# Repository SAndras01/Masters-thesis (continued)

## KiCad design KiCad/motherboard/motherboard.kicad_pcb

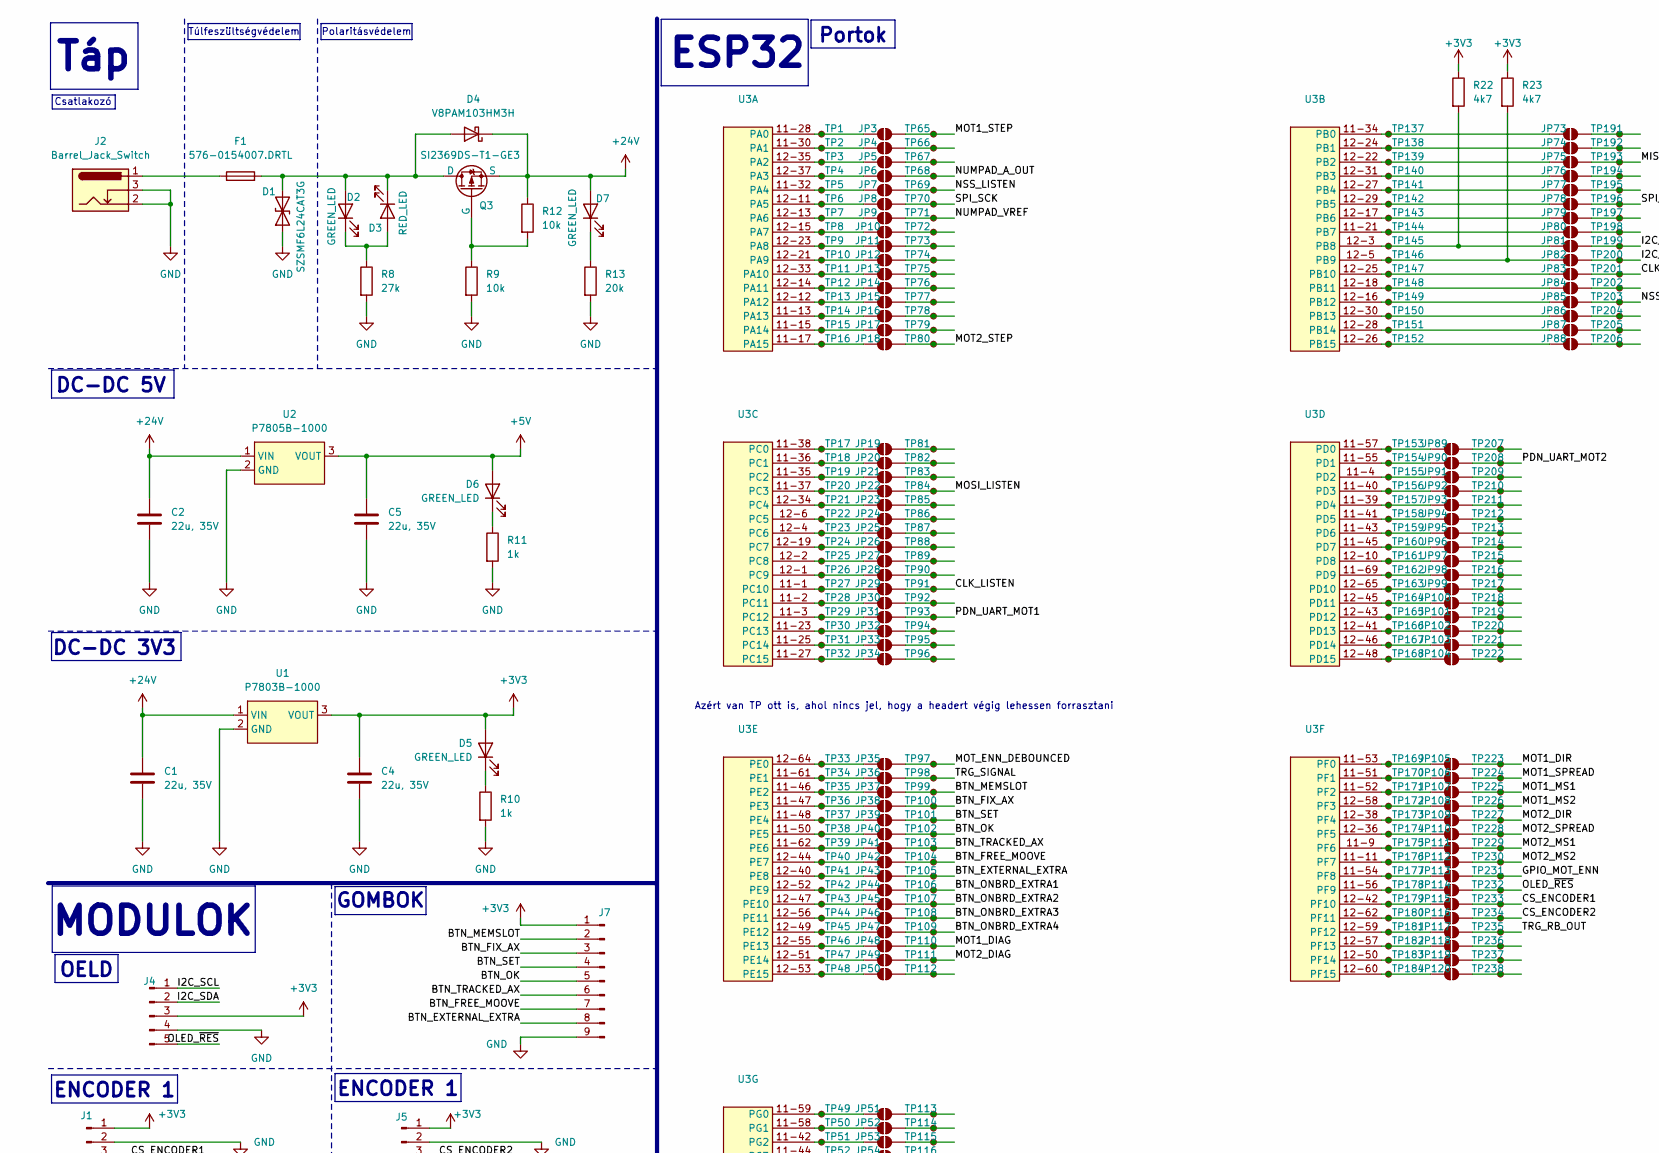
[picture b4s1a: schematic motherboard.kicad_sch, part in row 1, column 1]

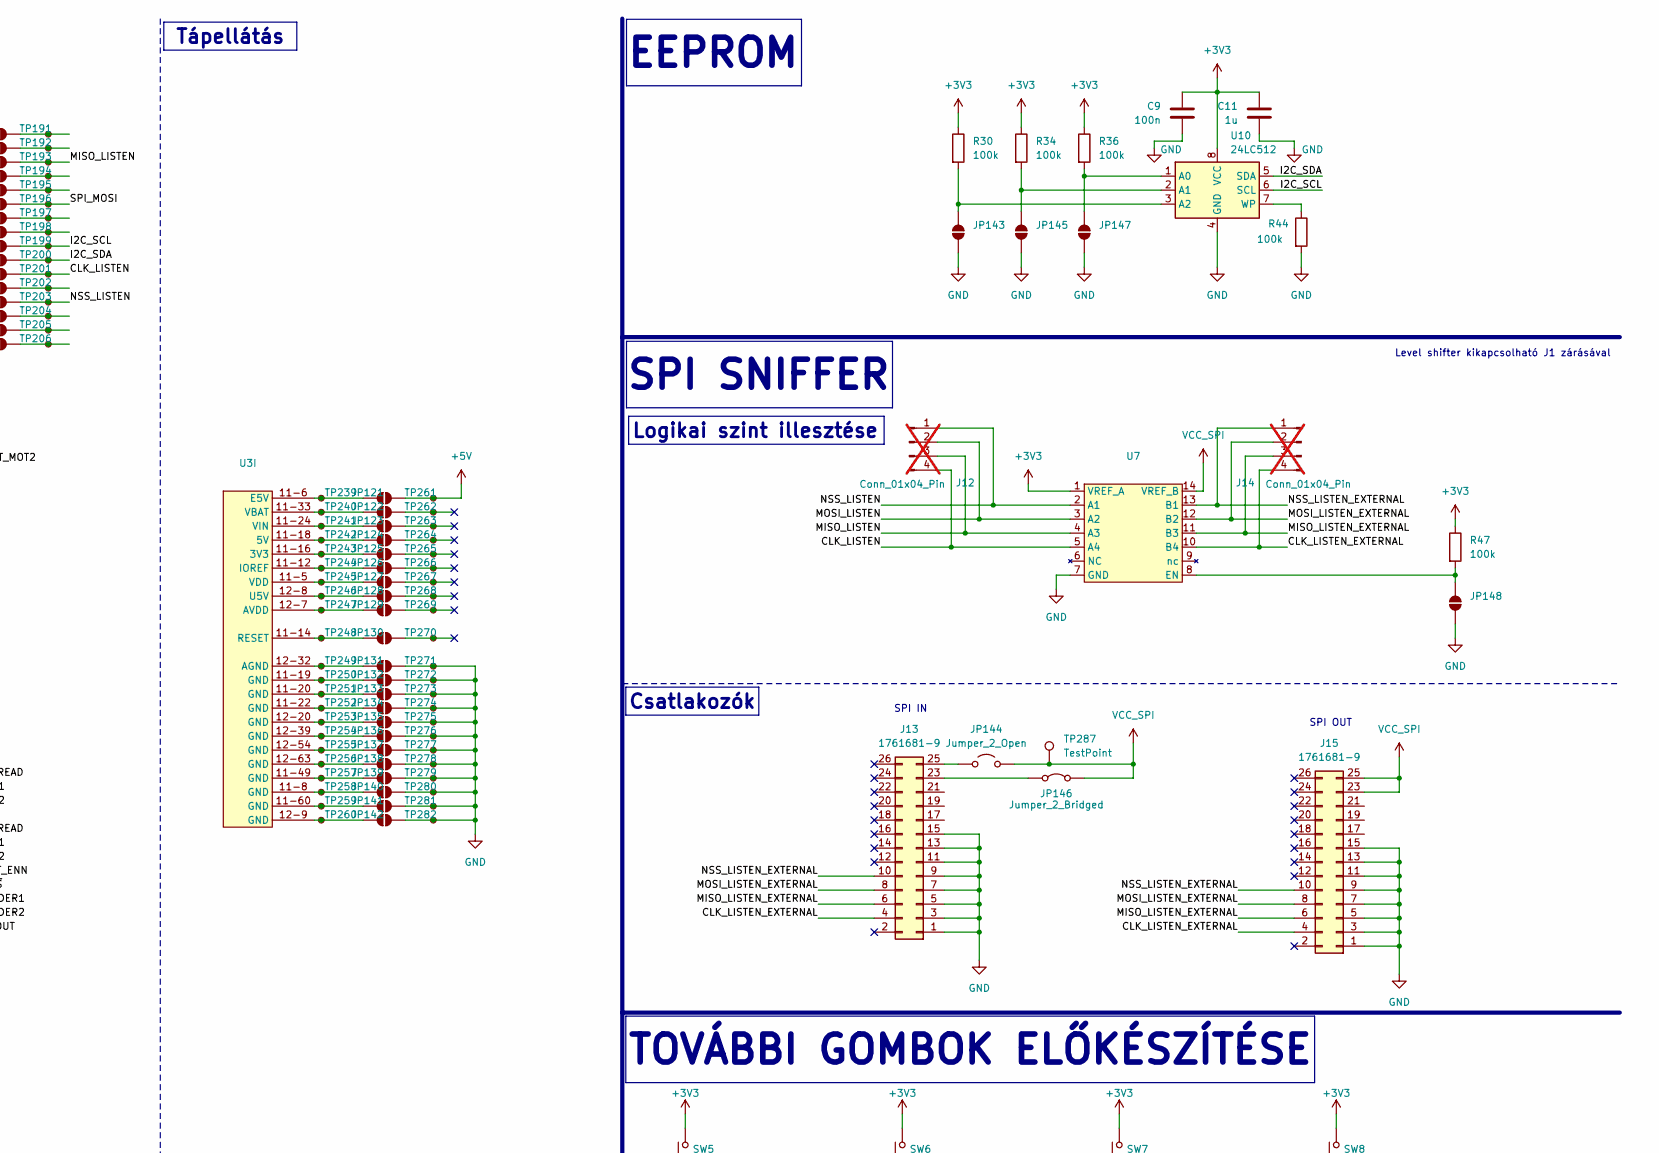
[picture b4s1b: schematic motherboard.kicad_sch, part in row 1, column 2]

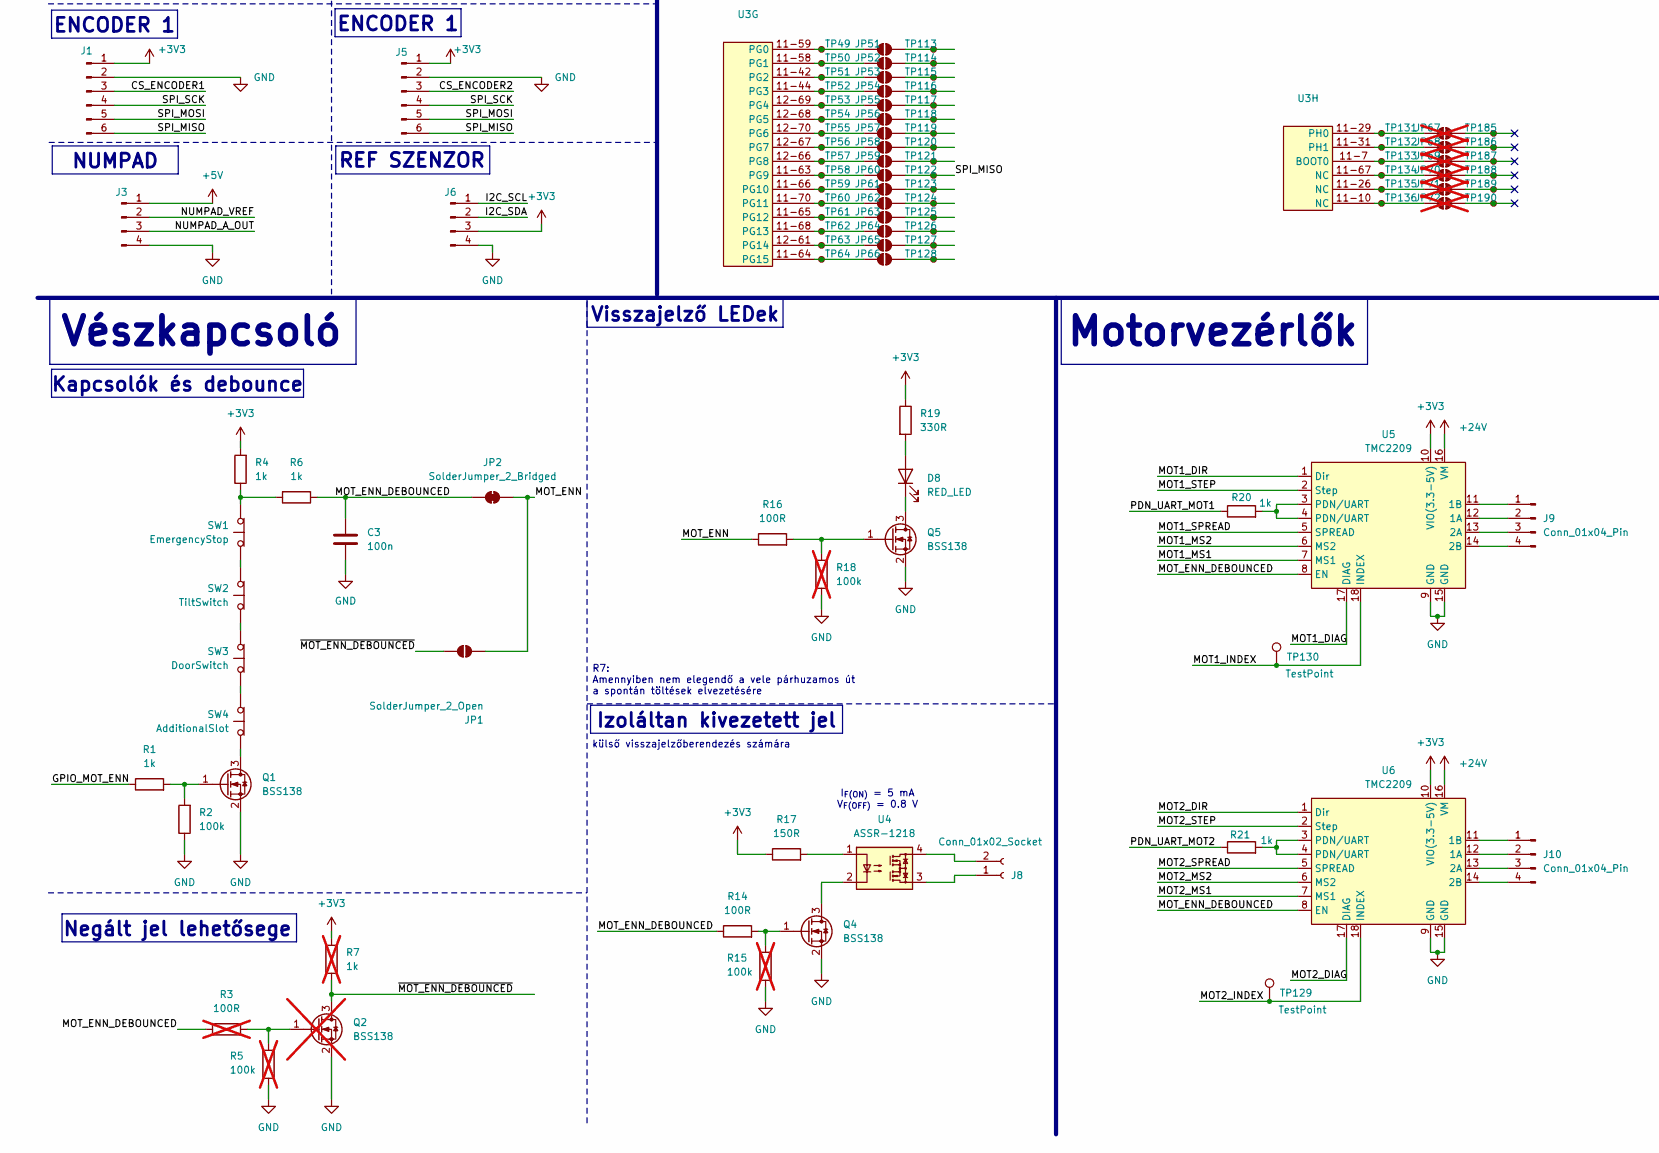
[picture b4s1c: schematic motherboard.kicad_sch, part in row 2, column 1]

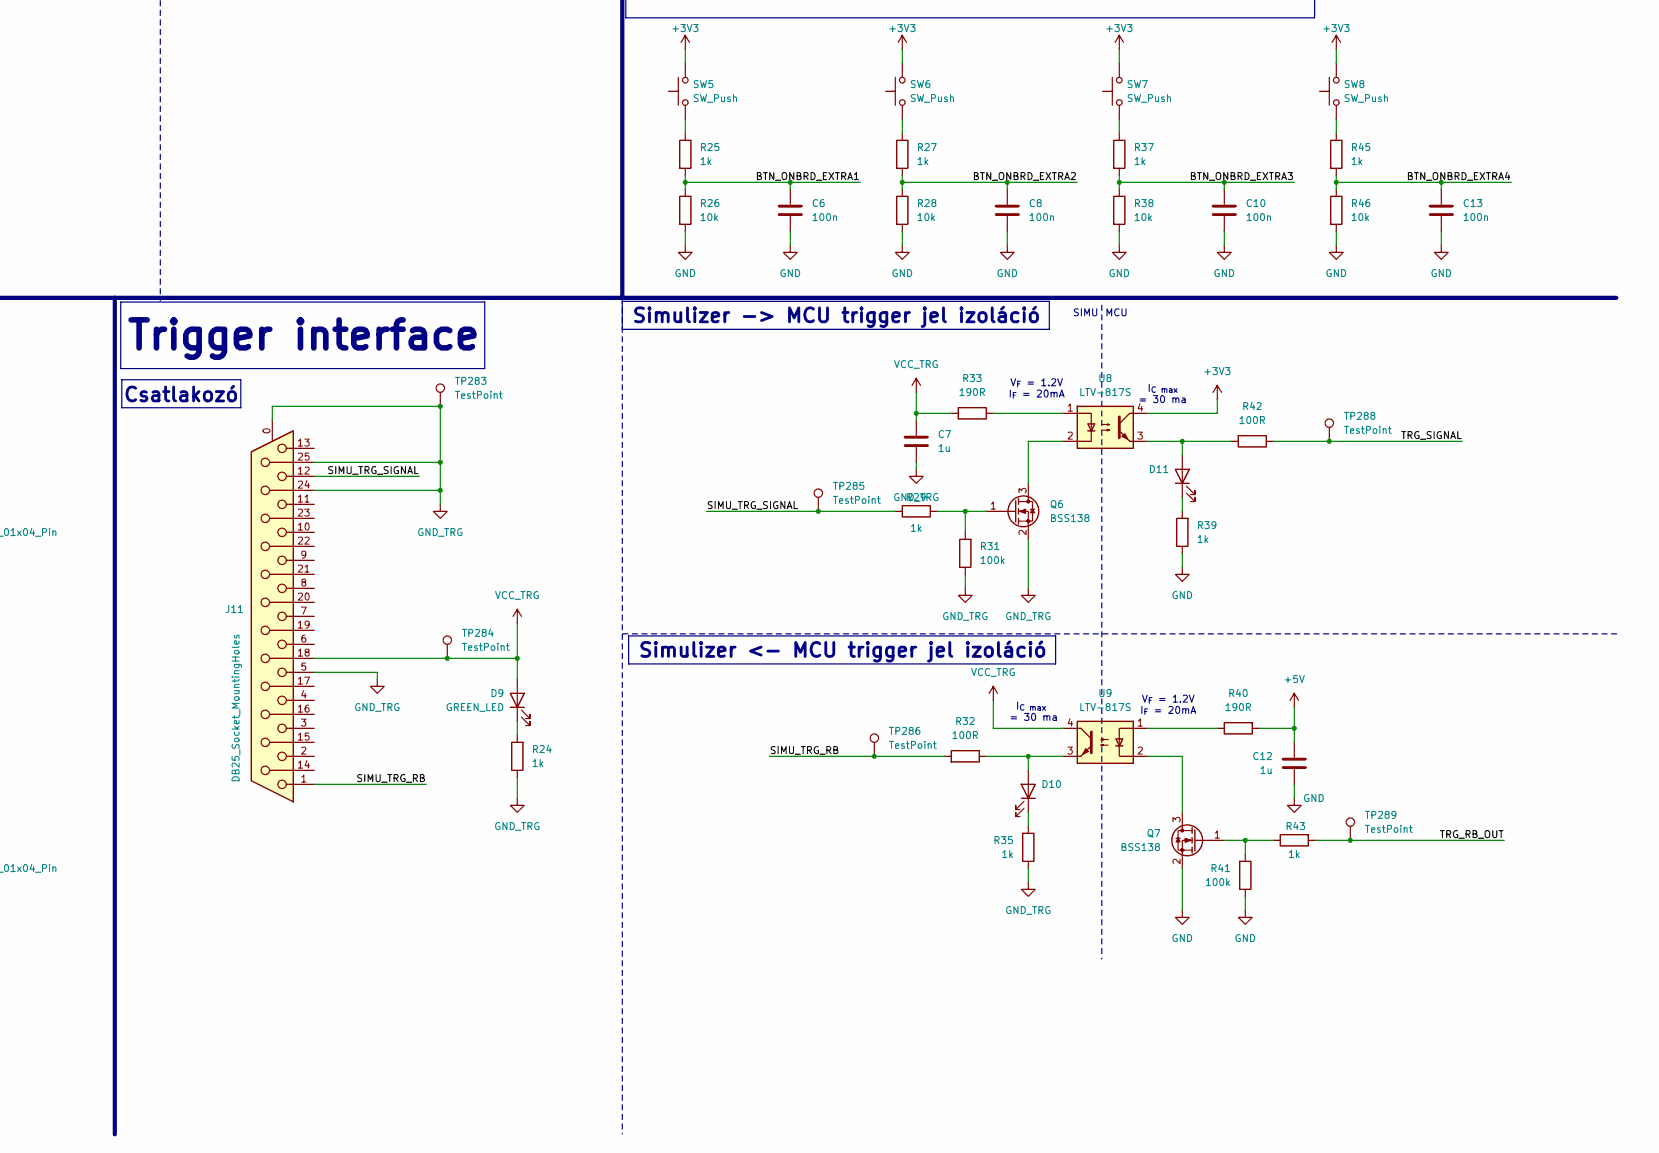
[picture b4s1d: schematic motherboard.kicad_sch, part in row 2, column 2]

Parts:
C1, C2, C4, C5: 22u, 35V; C_1206_3216Metric
C3, C6, C8, C9, C10, C13: 100n; C_0603_1608Metric
C7, C11, C12: 1u; C_0603_1608Metric
D1: SZSMF6L24CAT3G; D_SOD-123
D2, D5, D6, D7, D9, D10, D11: GREEN_LED; D_0603_1608Metric
D3, D8: RED_LED; D_0603_1608Metric
D4: V8PAM103HM3H; Vishay_SMPA
F1: 576-0154007.DRTL; Fuseholder_Littelfuse_Nano2_154x
J1, J5: Conn_01x06_Pin; JST_PH_B6B-PH-K_1x06_P2.00mm_Vertical
J2: Barrel_Jack_Switch; BarrelJack_Wuerth_694106106102_2.0x5.5mm
J3, J6, J9, J10: Conn_01x04_Pin; JST_PH_B4B-PH-K_1x04_P2.00mm_Vertical
J4: Conn_01x05_Pin; JST_PH_B5B-PH-K_1x05_P2.00mm_Vertical
J7: Conn_01x09_Pin; JST_PH_B9B-PH-K_1x09_P2.00mm_Vertical
J8: Conn_01x02_Socket; TerminalBlock_Phoenix_MKDS-1,5-2_1x02_P5.00mm_Horizontal
J11: DB25_Socket_MountingHoles; DSUB-25_Socket_Horizontal_P2.77x2.84mm_EdgePinOffset7.70mm_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
J12, J14: Conn_01x04_Pin; PinSocket_1x04_P2.54mm_Vertical; not fitted
J13, J15: 1761681-9; PinHeader_2x13_P2.54mm_Vertical
JP1: SolderJumper_2_Open; R_0603_1608Metric
JP2: SolderJumper_2_Bridged; R_0603_1608Metric
JP3, JP4, JP5, JP6, JP7, JP8, JP9, JP10, JP11, JP12, JP13, JP14, JP15, JP16, JP17, JP18, JP19, JP20, JP21, JP22, JP23, JP24, JP25, JP26, JP27, JP28, JP29, JP30, JP31, JP32, JP33, JP34, JP35, JP36, JP37, JP38, JP39, JP40, JP41, JP42, JP43, JP44, JP45, JP46, JP47, JP48, JP49, JP50, JP51, JP52, JP53, JP54, JP55, JP56, JP57, JP58, JP59, JP60, JP61, JP62, JP63, JP64, JP65, JP66, JP73, JP74, JP75, JP76, JP77, JP78, JP79, JP80, JP81, JP82, JP83, JP84, JP85, JP86, JP87, JP88, JP89, JP90, JP91, JP92, JP93, JP94, JP95, JP96, JP97, JP98, JP99, JP100, JP101, JP102, JP103, JP104, JP105, JP106, JP107, JP108, JP109, JP110, JP111, JP112, JP113, JP114, JP115, JP116, JP117, JP118, JP119, JP120, JP121, JP122, JP123, JP124, JP125, JP126, JP127, JP128, JP129, JP130, JP131, JP132, JP133, JP134, JP135, JP136, JP137, JP138, JP139, JP140, JP141, JP142: SolderJumper_2_Open; R_0603_1608Metric_Pad0.98x0.95mm_HandSolder
JP67, JP68, JP69, JP70, JP71, JP72: SolderJumper_2_Open; R_0603_1608Metric_Pad0.98x0.95mm_HandSolder; not fitted
JP143, JP145, JP147, JP148: SolderJumper_2_Open; SolderJumper-2_P1.3mm_Open_RoundedPad1.0x1.5mm
JP144: Jumper_2_Open; PinHeader_1x02_P2.54mm_Vertical
JP146: Jumper_2_Bridged; PinHeader_1x02_P2.54mm_Vertical
Q1, Q4, Q5, Q6, Q7: BSS138; SOT-23
Q2: BSS138; SOT-23; not fitted
Q3: SI2369DS-T1-GE3; TSOT-23
R1, R4, R6, R10, R11, R20, R21, R24, R25, R27, R29, R35, R37, R39, R43, R45: 1k; R_0603_1608Metric
R2, R30, R31, R34, R36, R41, R44, R47: 100k; R_0603_1608Metric
R3: 100R; R_0603_1608Metric; not fitted
R5, R15, R18: 100k; R_0603_1608Metric; not fitted
R7: 1k; R_0603_1608Metric; not fitted
R8: 27k; R_0603_1608Metric
R9, R12, R26, R28, R38, R46: 10k; R_0603_1608Metric
R13: 20k; R_0603_1608Metric
R14, R16, R32, R42: 100R; R_0603_1608Metric
R17: 150R; R_0603_1608Metric
R19: 330R; R_0603_1608Metric
R22, R23: 4k7; R_0603_1608Metric
R33, R40: 190R; R_0603_1608Metric
SW1: EmergencyStop; TerminalBlock_Phoenix_MKDS-1,5-2_1x02_P5.00mm_Horizontal
SW2: TiltSwitch; TerminalBlock_Phoenix_MKDS-1,5-2_1x02_P5.00mm_Horizontal
SW3: DoorSwitch; TerminalBlock_Phoenix_MKDS-1,5-2_1x02_P5.00mm_Horizontal
SW4: AdditionalSlot; TerminalBlock_Phoenix_MKDS-1,5-2_1x02_P5.00mm_Horizontal
SW5, SW6, SW7, SW8: SW_Push; PinSocket_1x02_P2.54mm_Vertical
TP1, TP2, TP3, TP4, TP5, TP6, TP7, TP8, TP9, TP10, TP11, TP12, TP13, TP14, TP15, TP16, TP17, TP18, TP19, TP20, TP21, TP22, TP23, TP24, TP25, TP26, TP27, TP28, TP29, TP30, TP31, TP32, TP33, TP34, TP35, TP36, TP37, TP38, TP39, TP40, TP41, TP42, TP43, TP44, TP45, TP46, TP47, TP48, TP49, TP50, TP51, TP52, TP53, TP54, TP55, TP56, TP57, TP58, TP59, TP60, TP61, TP62, TP63, TP64, TP65, TP66, TP67, TP68, TP69, TP70, TP71, TP72, TP73, TP74, TP75, TP76, TP77, TP78, TP79, TP80, TP81, TP82, TP83, TP84, TP85, TP86, TP87, TP88, TP89, TP90, TP91, TP92, TP93, TP94, TP95, TP96, TP97, TP98, TP99, TP100, TP101, TP102, TP103, TP104, TP105, TP106, TP107, TP108, TP109, TP110, TP111, TP112, TP113, TP114, TP115, TP116, TP117, TP118, TP119, TP120, TP121, TP122, TP123, TP124, TP125, TP126, TP127, TP128, TP131, TP132, TP133, TP134, TP135, TP136, TP137, TP138, TP139, TP140, TP141, TP142, TP143, TP144, TP145, TP146, TP147, TP148, TP149, TP150, TP151, TP152, TP153, TP154, TP155, TP156, TP157, TP158, TP159, TP160, TP161, TP162, TP163, TP164, TP165, TP166, TP167, TP168, TP169, TP170, TP171, TP172, TP173, TP174, TP175, TP176, TP177, TP178, TP179, TP180, TP181, TP182, TP183, TP184, TP185, TP186, TP187, TP188, TP189, TP190, TP191, TP192, TP193, TP194, TP195, TP196, TP197, TP198, TP199, TP200, TP201, TP202, TP203, TP204, TP205, TP206, TP207, TP208, TP209, TP210, TP211, TP212, TP213, TP214, TP215, TP216, TP217, TP218, TP219, TP220, TP221, TP222, TP223, TP224, TP225, TP226, TP227, TP228, TP229, TP230, TP231, TP232, TP233, TP234, TP235, TP236, TP237, TP238, TP239, TP240, TP241, TP242, TP243, TP244, TP245, TP246, TP247, TP248, TP249, TP250, TP251, TP252, TP253, TP254, TP255, TP256, TP257, TP258, TP259, TP260, TP261, TP262, TP263, TP264, TP265, TP266, TP267, TP268, TP269, TP270, TP271, TP272, TP273, TP274, TP275, TP276, TP277, TP278, TP279, TP280, TP281, TP282: TestPoint_Small; PinSocket_1x01_P2.54mm_Vertical
TP129, TP130: TestPoint; PinSocket_1x01_P2.54mm_Vertical
TP283, TP284, TP285, TP286, TP288, TP289: TestPoint; TestPoint_Pad_D2.0mm
TP287: TestPoint; PinHeader_1x01_P2.54mm_Vertical
U1: P7803B-1000; SIP3_11.6x8.5mm
U2: P7805B-1000; SIP3_11.6x8.5mm
U3: NUCLEO-F767ZI
U4: ASSR-1218; SO-4_4.4x4.3mm_P2.54mm
U5, U6: TMC2209; TMC2209 Silentstepstick
U7: TSSOP-14_4.4x5mm_P0.65mm
U8, U9: LTV-817S; SMDIP-4_W9.53mm
U10: 24LC512; SOIC-8_5.3x6.2mm_P1.27mm

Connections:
+3V3: C4.1, C9.1, C11.1, D5.2 (A), J1.1, J4.3, J5.1, J6.3, J7.1, R4.2, R7.2, R17.1, R19.1, R22.1, R23.1, R30.1, R34.1, R36.1, R47.1, SW5.2, SW6.2, SW7.2, SW8.2, U1.3 (VOUT), U5.10 (VIO(3.3-5V)), U6.10 (VIO(3.3-5V)), U7.1 (VREF_A), U8.4, U10.8 (VCC)
+5V: C5.1, C12.1, D6.2 (A), J3.1, JP121.2 (B), R40.2, TP261.1, U2.3 (VOUT)
+24V: C1.1, C2.1, D4.1 (K), D7.2 (A), Q3.3 (S), R12.1, U1.1 (VIN), U2.1 (VIN), U5.16 (VM), U6.16 (VM)
/BTN_EXTERNAL_EXTRA: J7.8, JP43.2 (B), TP105.1
/BTN_FIX_AX: J7.3, JP38.2 (B), TP100.1
/BTN_FREE_MOOVE: J7.7, JP42.2 (B), TP104.1
/BTN_MEMSLOT: J7.2, JP37.2 (B), TP99.1
/BTN_OK: J7.5, JP40.2 (B), TP102.1
/BTN_ONBRD_EXTRA1: C6.1, JP44.2 (B), R25.2, R26.1, TP106.1
/BTN_ONBRD_EXTRA2: C8.1, JP45.2 (B), R27.2, R28.1, TP107.1
/BTN_ONBRD_EXTRA3: C10.1, JP46.2 (B), R37.2, R38.1, TP108.1
/BTN_ONBRD_EXTRA4: C13.1, JP47.2 (B), R45.2, R46.1, TP109.1
/BTN_SET: J7.4, JP39.2 (B), TP101.1
/BTN_TRACKED_AX: J7.6, JP41.2 (B), TP103.1
/CLK_LISTEN: J12.4, JP29.2 (B), JP83.2 (B), TP91.1, TP201.1, U7.5 (A4)
/CLK_LISTEN_EXTERNAL: J13.4, J14.4, J15.4, U7.10 (B4)
/CS_ENCODER1: J1.3, JP115.2 (B), TP233.1
/CS_ENCODER2: J5.3, JP116.2 (B), TP234.1
/GPIO_MOT_ENN: JP113.2 (B), R1.1, TP231.1
/I2C_SCL: J4.1, J6.1, JP81.2 (B), TP199.1, U10.6 (SCL)
/I2C_SDA: J4.2, J6.2, JP82.2 (B), TP200.1, U10.5 (SDA)
/MISO_LISTEN: J12.3, JP75.2 (B), TP193.1, U7.4 (A3)
/MISO_LISTEN_EXTERNAL: J13.6, J14.3, J15.6, U7.11 (B3)
/MOSI_LISTEN: J12.2, JP22.2 (B), TP84.1, U7.3 (A2)
/MOSI_LISTEN_EXTERNAL: J13.8, J14.2, J15.8, U7.12 (B2)
/MOT1_DIAG: JP48.2 (B), TP110.1, U5.17 (DIAG)
/MOT1_DIR: JP105.2 (B), TP223.1, U5.1 (Dir)
/MOT1_INDEX: TP130.1, U5.18 (INDEX)
/MOT1_MS1: JP107.2 (B), TP225.1, U5.7 (MS1)
/MOT1_MS2: JP108.2 (B), TP226.1, U5.6 (MS2)
/MOT1_SPREAD: JP106.2 (B), TP224.1, U5.5 (SPREAD)
/MOT1_STEP: JP3.2 (B), TP65.1, U5.2 (Step)
/MOT2_DIAG: JP49.2 (B), TP111.1, U6.17 (DIAG)
/MOT2_DIR: JP109.2 (B), TP227.1, U6.1 (Dir)
/MOT2_INDEX: TP129.1, U6.18 (INDEX)
/MOT2_MS1: JP111.2 (B), TP229.1, U6.7 (MS1)
/MOT2_MS2: JP112.2 (B), TP230.1, U6.6 (MS2)
/MOT2_SPREAD: JP110.2 (B), TP228.1, U6.5 (SPREAD)
/MOT2_STEP: JP18.2 (B), TP80.1, U6.2 (Step)
/MOT_ENN: JP1.1 (A), JP2.2 (B), R16.1
/MOT_ENN_DEBOUNCED: C3.1, JP2.1 (A), JP35.2 (B), R3.1, R6.1, R14.1, TP97.1, U5.8 (EN), U6.8 (EN)
/NSS_LISTEN: J12.1, JP7.2 (B), JP85.2 (B), TP69.1, TP203.1, U7.2 (A1)
/NSS_LISTEN_EXTERNAL: J13.10, J14.1, J15.10, U7.13 (B1)
/NUMPAD_A_OUT: J3.3, JP6.2 (B), TP68.1
/NUMPAD_VREF: J3.2, JP9.2 (B), TP71.1
/OLED_~RES: J4.5, JP114.2 (B), TP232.1
/PDN_UART_MOT1: JP31.2 (B), R20.1, TP93.1
/PDN_UART_MOT2: JP90.2 (B), R21.1, TP208.1
/SIMU_TRG_RB: J11.1, R32.2, TP286.1
/SIMU_TRG_SIGNAL: J11.12, R29.2, TP285.1
/SPI_MISO: J1.6, J5.6, JP60.2 (B), TP122.1
/SPI_MOSI: J1.5, J5.5, JP78.2 (B), TP196.1
/SPI_SCK: J1.4, J5.4, JP8.2 (B), TP70.1
/TRG_RB_OUT: JP117.2 (B), R43.2, TP235.1, TP289.1
/TRG_SIGNAL: JP36.2 (B), R42.1, TP98.1, TP288.1
/~MOT_ENN_DEBOUNCED: JP1.2 (B), Q2.3 (D), R7.1
GND: C1.2, C2.2, C3.2, C4.2, C5.2, C6.2, C8.2, C9.2, C10.2, C11.2, C12.2, C13.2, D1.1 (A1), J1.2, J2.2, J2.3, J3.4, J4.4, J5.2, J6.4, J7.9, J13.1, J13.3, J13.5, J13.7, J13.9, J13.11, J13.13, J13.15, J15.1, J15.3, J15.5, J15.7, J15.9, J15.11, J15.13, J15.15, JP131.2 (B), JP132.2 (B), JP133.2 (B), JP134.2 (B), JP135.2 (B), JP136.2 (B), JP137.2 (B), JP138.2 (B), JP139.2 (B), JP140.2 (B), JP141.2 (B), JP142.2 (B), JP143.2 (B), JP145.2 (B), JP147.2 (B), JP148.2 (B), Q1.2 (S), Q2.2 (S), Q4.2 (S), Q5.2 (S), Q7.2 (S), R2.1, R5.1, R8.2, R9.2, R10.2, R11.2, R13.2, R15.1, R18.1, R26.2, R28.2, R38.2, R39.1, R41.1, R44.2, R46.2, TP271.1, TP272.1, TP273.1, TP274.1, TP275.1, TP276.1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
GND_TRG: C7.2, J11.0 (PAD), J11.5, J11.24, J11.25, Q6.2 (S), R24.1, R31.1, R35.1, TP283.1
unnamed: D1.2 (A2), D2.2 (A), D3.1 (K), D4.2 (A), F1.2, Q3.1 (D)
unnamed: D2.1 (K), D3.2 (A), R8.1
unnamed: D5.1 (K), R10.1
unnamed: D6.1 (K), R11.1
unnamed: D7.1 (K), R13.1
unnamed: D8.2 (A), R19.2
unnamed: D8.1 (K), Q5.3 (D)
unnamed: D9.1 (K), R24.2
unnamed: D10.2 (A), R32.1, U9.3
unnamed: D10.1 (K), R35.2
unnamed: D11.2 (A), R42.2, U8.3
unnamed: D11.1 (K), R39.2
unnamed: F1.1, J2.1
unnamed: J8.1, U4.3
unnamed: J8.2, U4.4
unnamed: J9.1, U5.11 (1B)
unnamed: J9.2, U5.12 (1A)
unnamed: J9.3, U5.13 (2A)
unnamed: J9.4, U5.14 (2B)
unnamed: J10.1, U6.11 (1B)
unnamed: J10.2, U6.12 (1A)
unnamed: J10.3, U6.13 (2A)
unnamed: J10.4, U6.14 (2B)
unnamed: J13.23, JP146.1 (A)
unnamed: J13.25, JP144.1 (A)
unnamed: JP3.1 (A), TP1.1, U3.11-28 (PA0)
unnamed: JP4.1 (A), TP2.1, U3.11-30 (PA1)
unnamed: JP4.2 (B), TP66.1
unnamed: JP5.1 (A), TP3.1, U3.12-35 (PA2)
unnamed: JP5.2 (B), TP67.1
unnamed: JP6.1 (A), TP4.1, U3.12-37 (PA3)
unnamed: JP7.1 (A), TP5.1, U3.11-32 (PA4)
unnamed: JP8.1 (A), TP6.1, U3.12-11 (PA5)
unnamed: JP9.1 (A), TP7.1, U3.12-13 (PA6)
unnamed: JP10.1 (A), TP8.1, U3.12-15 (PA7)
unnamed: JP10.2 (B), TP72.1
unnamed: JP11.1 (A), TP9.1, U3.12-23 (PA8)
unnamed: JP11.2 (B), TP73.1
unnamed: JP12.1 (A), TP10.1, U3.12-21 (PA9)
unnamed: JP12.2 (B), TP74.1
unnamed: JP13.1 (A), TP11.1, U3.12-33 (PA10)
unnamed: JP13.2 (B), TP75.1
unnamed: JP14.1 (A), TP12.1, U3.12-14 (PA11)
unnamed: JP14.2 (B), TP76.1
unnamed: JP15.1 (A), TP13.1, U3.12-12 (PA12)
unnamed: JP15.2 (B), TP77.1
unnamed: JP16.1 (A), TP14.1, U3.11-13 (PA13)
unnamed: JP16.2 (B), TP78.1
unnamed: JP17.1 (A), TP15.1, U3.11-15 (PA14)
unnamed: JP17.2 (B), TP79.1
unnamed: JP18.1 (A), TP16.1, U3.11-17 (PA15)
unnamed: JP19.1 (A), TP17.1, U3.11-38 (PC0)
unnamed: JP19.2 (B), TP81.1
unnamed: JP20.1 (A), TP18.1, U3.11-36 (PC1)
unnamed: JP20.2 (B), TP82.1
unnamed: JP21.1 (A), TP19.1, U3.11-35 (PC2)
unnamed: JP21.2 (B), TP83.1
unnamed: JP22.1 (A), TP20.1, U3.11-37 (PC3)
unnamed: JP23.1 (A), TP21.1, U3.12-34 (PC4)
unnamed: JP23.2 (B), TP85.1
unnamed: JP24.1 (A), TP22.1, U3.12-6 (PC5)
unnamed: JP24.2 (B), TP86.1
unnamed: JP25.1 (A), TP23.1, U3.12-4 (PC6)
unnamed: JP25.2 (B), TP87.1
unnamed: JP26.1 (A), TP24.1, U3.12-19 (PC7)
unnamed: JP26.2 (B), TP88.1
unnamed: JP27.1 (A), TP25.1, U3.12-2 (PC8)
unnamed: JP27.2 (B), TP89.1
unnamed: JP28.1 (A), TP26.1, U3.12-1 (PC9)
unnamed: JP28.2 (B), TP90.1
unnamed: JP29.1 (A), TP27.1, U3.11-1 (PC10)
unnamed: JP30.1 (A), TP28.1, U3.11-2 (PC11)
unnamed: JP30.2 (B), TP92.1
unnamed: JP31.1 (A), TP29.1, U3.11-3 (PC12)
unnamed: JP32.1 (A), TP30.1, U3.11-23 (PC13)
unnamed: JP32.2 (B), TP94.1
unnamed: JP33.1 (A), TP31.1, U3.11-25 (PC14)
unnamed: JP33.2 (B), TP95.1
unnamed: JP34.1 (A), TP32.1, U3.11-27 (PC15)
unnamed: JP34.2 (B), TP96.1
unnamed: JP35.1 (A), TP33.1, U3.12-64 (PE0)
unnamed: JP36.1 (A), TP34.1, U3.11-61 (PE1)
unnamed: JP37.1 (A), TP35.1, U3.11-46 (PE2)
unnamed: JP38.1 (A), TP36.1, U3.11-47 (PE3)
unnamed: JP39.1 (A), TP37.1, U3.11-48 (PE4)
unnamed: JP40.1 (A), TP38.1, U3.11-50 (PE5)
unnamed: JP41.1 (A), TP39.1, U3.11-62 (PE6)
unnamed: JP42.1 (A), TP40.1, U3.12-44 (PE7)
unnamed: JP43.1 (A), TP41.1, U3.12-40 (PE8)
unnamed: JP44.1 (A), TP42.1, U3.12-52 (PE9)
unnamed: JP45.1 (A), TP43.1, U3.12-47 (PE10)
unnamed: JP46.1 (A), TP44.1, U3.12-56 (PE11)
unnamed: JP47.1 (A), TP45.1, U3.12-49 (PE12)
unnamed: JP48.1 (A), TP46.1, U3.12-55 (PE13)
unnamed: JP49.1 (A), TP47.1, U3.12-51 (PE14)
unnamed: JP50.1 (A), TP48.1, U3.12-53 (PE15)
unnamed: JP50.2 (B), TP112.1
unnamed: JP51.1 (A), TP49.1, U3.11-59 (PG0)
unnamed: JP51.2 (B), TP113.1
unnamed: JP52.1 (A), TP50.1, U3.11-58 (PG1)
unnamed: JP52.2 (B), TP114.1
unnamed: JP53.1 (A), TP51.1, U3.11-42 (PG2)
unnamed: JP53.2 (B), TP115.1
unnamed: JP54.1 (A), TP52.1, U3.11-44 (PG3)
unnamed: JP54.2 (B), TP116.1
unnamed: JP55.1 (A), TP53.1, U3.12-69 (PG4)
unnamed: JP55.2 (B), TP117.1
unnamed: JP56.1 (A), TP54.1, U3.12-68 (PG5)
unnamed: JP56.2 (B), TP118.1
unnamed: JP57.1 (A), TP55.1, U3.12-70 (PG6)
unnamed: JP57.2 (B), TP119.1
unnamed: JP58.1 (A), TP56.1, U3.12-67 (PG7)
unnamed: JP58.2 (B), TP120.1
unnamed: JP59.1 (A), TP57.1, U3.12-66 (PG8)
unnamed: JP59.2 (B), TP121.1
unnamed: JP60.1 (A), TP58.1, U3.11-63 (PG9)
unnamed: JP61.1 (A), TP59.1, U3.11-66 (PG10)
unnamed: JP61.2 (B), TP123.1
unnamed: JP62.1 (A), TP60.1, U3.11-70 (PG11)
unnamed: JP62.2 (B), TP124.1
unnamed: JP63.1 (A), TP61.1, U3.11-65 (PG12)
unnamed: JP63.2 (B), TP125.1
unnamed: JP64.1 (A), TP62.1, U3.11-68 (PG13)
unnamed: JP64.2 (B), TP126.1
unnamed: JP65.1 (A), TP63.1, U3.12-61 (PG14)
unnamed: JP65.2 (B), TP127.1
unnamed: JP66.1 (A), TP64.1, U3.11-64 (PG15)
unnamed: JP66.2 (B), TP128.1
unnamed: JP67.1 (A), TP131.1, U3.11-29 (PH0)
unnamed: JP68.1 (A), TP132.1, U3.11-31 (PH1)
unnamed: JP69.1 (A), TP133.1, U3.11-7 (BOOT0)
unnamed: JP70.1 (A), TP134.1, U3.11-67 (NC)
unnamed: JP71.1 (A), TP135.1, U3.11-26 (NC)
unnamed: JP72.1 (A), TP136.1, U3.11-10 (NC)
unnamed: JP73.1 (A), TP137.1, U3.11-34 (PB0)
unnamed: JP73.2 (B), TP191.1
unnamed: JP74.1 (A), TP138.1, U3.12-24 (PB1)
unnamed: JP74.2 (B), TP192.1
unnamed: JP75.1 (A), TP139.1, U3.12-22 (PB2)
unnamed: JP76.1 (A), TP140.1, U3.12-31 (PB3)
unnamed: JP76.2 (B), TP194.1
unnamed: JP77.1 (A), TP141.1, U3.12-27 (PB4)
unnamed: JP77.2 (B), TP195.1
unnamed: JP78.1 (A), TP142.1, U3.12-29 (PB5)
unnamed: JP79.1 (A), TP143.1, U3.12-17 (PB6)
unnamed: JP79.2 (B), TP197.1
unnamed: JP80.1 (A), TP144.1, U3.11-21 (PB7)
unnamed: JP80.2 (B), TP198.1
unnamed: JP81.1 (A), R22.2, TP145.1, U3.12-3 (PB8)
unnamed: JP82.1 (A), R23.2, TP146.1, U3.12-5 (PB9)
unnamed: JP83.1 (A), TP147.1, U3.12-25 (PB10)
unnamed: JP84.1 (A), TP148.1, U3.12-18 (PB11)
unnamed: JP84.2 (B), TP202.1
unnamed: JP85.1 (A), TP149.1, U3.12-16 (PB12)
unnamed: JP86.1 (A), TP150.1, U3.12-30 (PB13)
unnamed: JP86.2 (B), TP204.1
unnamed: JP87.1 (A), TP151.1, U3.12-28 (PB14)
unnamed: JP87.2 (B), TP205.1
unnamed: JP88.1 (A), TP152.1, U3.12-26 (PB15)
unnamed: JP88.2 (B), TP206.1
unnamed: JP89.1 (A), TP153.1, U3.11-57 (PD0)
unnamed: JP89.2 (B), TP207.1
unnamed: JP90.1 (A), TP154.1, U3.11-55 (PD1)
unnamed: JP91.1 (A), TP155.1, U3.11-4 (PD2)
unnamed: JP91.2 (B), TP209.1
unnamed: JP92.1 (A), TP156.1, U3.11-40 (PD3)
unnamed: JP92.2 (B), TP210.1
unnamed: JP93.1 (A), TP157.1, U3.11-39 (PD4)
unnamed: JP93.2 (B), TP211.1
unnamed: JP94.1 (A), TP158.1, U3.11-41 (PD5)
unnamed: JP94.2 (B), TP212.1
unnamed: JP95.1 (A), TP159.1, U3.11-43 (PD6)
unnamed: JP95.2 (B), TP213.1
unnamed: JP96.1 (A), TP160.1, U3.11-45 (PD7)
unnamed: JP96.2 (B), TP214.1
unnamed: JP97.1 (A), TP161.1, U3.12-10 (PD8)
unnamed: JP97.2 (B), TP215.1
unnamed: JP98.1 (A), TP162.1, U3.11-69 (PD9)
unnamed: JP98.2 (B), TP216.1
unnamed: JP99.1 (A), TP163.1, U3.12-65 (PD10)
unnamed: JP99.2 (B), TP217.1
unnamed: JP100.1 (A), TP164.1, U3.12-45 (PD11)
unnamed: JP100.2 (B), TP218.1
unnamed: JP101.1 (A), TP165.1, U3.12-43 (PD12)
unnamed: JP101.2 (B), TP219.1
unnamed: JP102.1 (A), TP166.1, U3.12-41 (PD13)
unnamed: JP102.2 (B), TP220.1
unnamed: JP103.1 (A), TP167.1, U3.12-46 (PD14)
unnamed: JP103.2 (B), TP221.1
unnamed: JP104.1 (A), TP168.1, U3.12-48 (PD15)
unnamed: JP104.2 (B), TP222.1
unnamed: JP105.1 (A), TP169.1, U3.11-53 (PF0)
unnamed: JP106.1 (A), TP170.1, U3.11-51 (PF1)
unnamed: JP107.1 (A), TP171.1, U3.11-52 (PF2)
unnamed: JP108.1 (A), TP172.1, U3.12-58 (PF3)
unnamed: JP109.1 (A), TP173.1, U3.12-38 (PF4)
unnamed: JP110.1 (A), TP174.1, U3.12-36 (PF5)
unnamed: JP111.1 (A), TP175.1, U3.11-9 (PF6)
unnamed: JP112.1 (A), TP176.1, U3.11-11 (PF7)
unnamed: JP113.1 (A), TP177.1, U3.11-54 (PF8)
unnamed: JP114.1 (A), TP178.1, U3.11-56 (PF9)
unnamed: JP115.1 (A), TP179.1, U3.12-42 (PF10)
unnamed: JP116.1 (A), TP180.1, U3.12-62 (PF11)
unnamed: JP117.1 (A), TP181.1, U3.12-59 (PF12)
unnamed: JP118.1 (A), TP182.1, U3.12-57 (PF13)
unnamed: JP118.2 (B), TP236.1
unnamed: JP119.1 (A), TP183.1, U3.12-50 (PF14)
unnamed: JP119.2 (B), TP237.1
unnamed: JP120.1 (A), TP184.1, U3.12-60 (PF15)
unnamed: JP120.2 (B), TP238.1
unnamed: JP121.1 (A), TP239.1, U3.11-6 (E5V)
unnamed: JP122.1 (A), TP240.1, U3.11-33 (VBAT)
unnamed: JP123.1 (A), TP241.1, U3.11-24 (VIN)
unnamed: JP124.1 (A), TP242.1, U3.11-18 (5V)
unnamed: JP125.1 (A), TP243.1, U3.11-16 (3V3)
unnamed: JP126.1 (A), TP244.1, U3.11-12 (IOREF)
unnamed: JP127.1 (A), TP245.1, U3.11-5 (VDD)
unnamed: JP128.1 (A), TP246.1, U3.12-8 (U5V)
unnamed: JP129.1 (A), TP247.1, U3.12-7 (AVDD)
unnamed: JP130.1 (A), TP248.1, U3.11-14 (RESET)
unnamed: JP131.1 (A), TP249.1, U3.12-32 (AGND)
unnamed: JP132.1 (A), TP250.1, U3.11-19 (GND)
unnamed: JP133.1 (A), TP251.1, U3.11-20 (GND)
unnamed: JP134.1 (A), TP252.1, U3.11-22 (GND)
unnamed: JP135.1 (A), TP253.1, U3.12-20 (GND)
unnamed: JP136.1 (A), TP254.1, U3.12-39 (GND)
unnamed: JP137.1 (A), TP255.1, U3.12-54 (GND)
unnamed: JP138.1 (A), TP256.1, U3.12-63 (GND)
unnamed: JP139.1 (A), TP257.1, U3.11-49 (GND)
unnamed: JP140.1 (A), TP258.1, U3.11-8 (GND)
unnamed: JP141.1 (A), TP259.1, U3.11-60 (GND)
unnamed: JP142.1 (A), TP260.1, U3.12-9 (GND)
unnamed: JP143.1 (A), R30.2, U10.3 (A2)
unnamed: JP145.1 (A), R34.2, U10.2 (A1)
unnamed: JP147.1 (A), R36.2, U10.1 (A0)
unnamed: JP148.1 (A), R47.2, U7.8 (EN)
unnamed: Q1.3 (D), SW4.1 (A)
unnamed: Q1.1 (G), R1.2, R2.2
unnamed: Q2.1 (G), R3.2, R5.2
unnamed: Q3.2 (G), R9.1, R12.2
unnamed: Q4.3 (D), U4.2
unnamed: Q4.1 (G), R14.2, R15.2
unnamed: Q5.1 (G), R16.2, R18.2
unnamed: Q6.3 (D), U8.2
unnamed: Q6.1 (G), R29.1, R31.2
unnamed: Q7.3 (D), U9.2
unnamed: Q7.1 (G), R41.2, R43.1
unnamed: R17.2, U4.1
unnamed: R20.2, U5.3 (PDN/UART), U5.4 (PDN/UART)
unnamed: R21.2, U6.3 (PDN/UART), U6.4 (PDN/UART)
unnamed: R25.1, SW5.1
unnamed: R27.1, SW6.1
unnamed: R33.1, U8.1
unnamed: R37.1, SW7.1
unnamed: R40.1, U9.1
unnamed: R45.1, SW8.1
unnamed: SW1.1 (A), SW2.2 (B)
unnamed: R4.1, R6.2, SW1.2 (B)
unnamed: SW2.1 (A), SW3.2 (B)
unnamed: SW3.1 (A), SW4.2 (B)
unnamed: R44.1, U10.7 (WP)
VCC_SPI: J15.23, J15.25, JP144.2 (B), JP146.2 (B), TP287.1, U7.14 (VREF_B)
VCC_TRG: C7.1, D9.2 (A), J11.18, R33.2, TP284.1, U9.4

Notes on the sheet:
Portok
V_{F} = 1.2V I_{F} = 20mA
külső visszajelzőberendezés számára
I_{C max} = 30 ma
SIMU
ENCODER 1
MODULOK
Kapcsolók és debounce
Visszajelző LEDek
SPI OUT
Negált jel lehetősege
OELD
R7: Amennyiben nem elegendő a vele párhuzamos út a spontán töltések elvezetésére
Trigger interface
Simulizer <- MCU trigger jel izoláció
SPI IN
DC-DC 3V3
Túlfeszültségvédelem
Csatlakozók
GOMBOK
Level shifter kikapcsolható J1 zárásával
Azért van TP ott is, ahol nincs jel, hogy a headert végig lehessen forrasztani
Simulizer -> MCU trigger jel izoláció
ESP32
NUMPAD
EEPROM
DC-DC 5V
MCU
Tápellátás
Izoláltan kivezetett jel
Táp
SPI SNIFFER
Vészkapcsoló
I_{F(ON)} = 5 mA V_{F(OFF)} = 0.8 V
REF SZENZOR
TOVÁBBI GOMBOK ELŐKÉSZÍTÉSE
Logikai szint illesztése
I_{C max} = 30 ma
Csatlakozó
Motorvezérlők

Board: 2 copper layers, 549 parts (0 on the bottom side), 321 nets, no tracks yet.

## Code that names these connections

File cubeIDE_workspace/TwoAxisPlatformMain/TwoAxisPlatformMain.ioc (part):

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Mcu.Name=STM32F767ZITx
Mcu.Package=LQFP144
Mcu.UserName=STM32F767ZITx
PA0/WKUP.GPIOParameters=GPIO_Speed,GPIO_Label
PA0/WKUP.GPIO_Label=MOT1_STEP
PA0/WKUP.GPIO_Speed=GPIO_SPEED_FREQ_HIGH
PA0/WKUP.Signal=S_TIM5_CH1
PA1.GPIOParameters=GPIO_Label
PA1.GPIO_Label=RMII_REF_CLK [LAN8742A-CZ-TR_REFCLK0]
PA1.Mode=RMII
PA1.Signal=ETH_REF_CLK
PA10.GPIOParameters=GPIO_Label
PA10.GPIO_Label=USB_ID
PA10.Signal=USB_OTG_FS_ID
PA11.GPIOParameters=GPIO_Label
PA11.GPIO_Label=USB_DM
PA11.Mode=Device_Only
PA11.Signal=USB_OTG_FS_DM
PA12.GPIOParameters=GPIO_Label
PA12.GPIO_Label=USB_DP
PA12.Mode=Device_Only
PA12.Signal=USB_OTG_FS_DP
PA13.GPIOParameters=GPIO_Label
PA13.GPIO_Label=TMS
PA13.Mode=Serial_Wire
PA13.Signal=SYS_JTMS-SWDIO
PA14.GPIOParameters=GPIO_Label
PA14.GPIO_Label=TCK
PA14.Mode=Serial_Wire
PA14.Signal=SYS_JTCK-SWCLK
PA15.GPIOParameters=GPIO_Speed,GPIO_Label
PA15.GPIO_Label=MOT2_STEP
PA15.GPIO_Speed=GPIO_SPEED_FREQ_HIGH
PA15.Signal=S_TIM2_CH1_ETR
PA2.GPIOParameters=GPIO_Label
PA2.GPIO_Label=RMII_MDIO [LAN8742A-CZ-TR_MDIO]
PA2.Mode=RMII
PA2.Signal=ETH_MDIO
PA3.GPIOParameters=GPIO_Label
PA3.GPIO_Label=NUMPAD_A_OUT
PA3.Signal=ADCx_IN3
PA4.Mode=NSS_Signal_Hard_Input
PA4.Signal=SPI3_NSS
PA5.Mode=Full_Duplex_Master
PA5.Signal=SPI1_SCK
PA6.GPIOParameters=GPIO_Label
PA6.GPIO_Label=NUMPAD_VREF
PA6.Signal=ADCx_IN6
PA7.GPIOParameters=GPIO_Label
PA7.GPIO_Label=RMII_CRS_DV [LAN8742A-CZ-TR_CRS_DV]
PA7.Mode=RMII
PA7.Signal=ETH_CRS_DV
PA8.GPIOParameters=GPIO_Label
PA8.GPIO_Label=USB_SOF [TP1]
PA8.Mode=Activate_SOF_FS
PA8.Signal=USB_OTG_FS_SOF
PA9.GPIOParameters=GPIO_Label
PA9.GPIO_Label=USB_VBUS
PA9.Mode=Activate_VBUS
PA9.Signal=USB_OTG_FS_VBUS
PB0.GPIOParameters=GPIO_Label
PB0.GPIO_Label=LD1 [Green]
PB0.Signal=GPIO_Output
PB10.Mode=RX_Only_Simplex_Unidirect_Slave
PB10.Signal=SPI2_SCK
PB12.Mode=NSS_Signal_Hard_Input
PB12.Signal=SPI2_NSS
PB13.GPIOParameters=GPIO_Label
PB13.GPIO_Label=RMII_TXD1 [LAN8742A-CZ-TR_TXD1]
PB13.Mode=RMII
PB13.Signal=ETH_TXD1
PB14.GPIOParameters=GPIO_Label
PB14.GPIO_Label=LD3 [Red]
PB14.Signal=GPIO_Output
PB2.Mode=RX_Only_Simplex_Unidirect_Slave
PB2.Signal=SPI3_MOSI
PB3.GPIOParameters=GPIO_Label
PB3.GPIO_Label=SWO
PB3.Signal=SYS_JTDO-SWO
PB5.Mode=Full_Duplex_Master
PB5.Signal=SPI1_MOSI
PB7.GPIOParameters=GPIO_Label
PB7.GPIO_Label=LD2 [Blue]
PB7.Signal=GPIO_Output
PB8.Mode=I2C
PB8.Signal=I2C1_SCL
PB9.Mode=I2C
PB9.Signal=I2C1_SDA
PC1.GPIOParameters=GPIO_Label
PC1.GPIO_Label=RMII_MDC [LAN8742A-CZ-TR_MDC]
PC1.Mode=RMII
PC1.Signal=ETH_MDC
PC10.Mode=RX_Only_Simplex_Unidirect_Slave
PC10.Signal=SPI3_SCK
PC13.GPIOParameters=GPIO_Label
PC13.GPIO_Label=USER_Btn [B1]
PC13.Signal=GPXTI13
PC14/OSC32_IN.Mode=LSE-External-Oscillator
PC14/OSC32_IN.Signal=RCC_OSC32_IN
PC15/OSC32_OUT.Mode=LSE-External-Oscillator
PC15/OSC32_OUT.Signal=RCC_OSC32_OUT
PC2.GPIOParameters=GPIO_Label
PC2.GPIO_Label=TRG_RB_OUT
PC2.Signal=GPIO_Output
PC3.Mode=RX_Only_Simplex_Unidirect_Slave
PC3.Signal=SPI2_MOSI
PC4.GPIOParameters=GPIO_Label
PC4.GPIO_Label=RMII_RXD0 [LAN8742A-CZ-TR_RXD0]
PC4.Mode=RMII
PC4.Signal=ETH_RXD0
PC5.GPIOParameters=GPIO_Label
PC5.GPIO_Label=RMII_RXD1 [LAN8742A-CZ-TR_RXD1]
PC5.Mode=RMII
PC5.Signal=ETH_RXD1
PD8.GPIOParameters=GPIO_Label
PD8.GPIO_Label=STLK_RX [STM32F103CBT6_PA3]
PD8.Mode=Asynchronous
PD8.Signal=USART3_TX
PD9.GPIOParameters=GPIO_Label
PD9.GPIO_Label=STLK_TX [STM32F103CBT6_PA2]
PD9.Mode=Asynchronous
PD9.Signal=USART3_RX
PE0.GPIOParameters=GPIO_Label
PE0.GPIO_Label=MOT_ENN_RB
PE0.Signal=GPIO_Input
PE1.GPIOParameters=GPIO_Label
PE1.GPIO_Label=TRG_SIGNAL
PE1.Signal=GPIO_Input
PE10.GPIOParameters=GPIO_Label
PE10.GPIO_Label=BTN_ONBRD_EXTRA2
PE10.Signal=GPIO_Input
PE11.GPIOParameters=GPIO_Label
PE11.GPIO_Label=BTN_ONBRD_EXTRA3
PE11.Signal=GPIO_Input
PE12.GPIOParameters=GPIO_Label
PE12.GPIO_Label=BTN_ONBRD_EXTRA4
PE12.Signal=GPIO_Input
PE13.GPIOParameters=GPIO_Label
PE13.GPIO_Label=MOT1_DIAG
PE13.Signal=GPIO_Input
PE14.GPIOParameters=GPIO_Label
PE14.GPIO_Label=MOT2_DIAG
PE14.Signal=GPIO_Input
PE2.GPIOParameters=GPIO_Label
PE2.GPIO_Label=BTN_FIX_AX
PE2.Signal=GPIO_Input
PE3.GPIOParameters=GPIO_Label
PE3.GPIO_Label=BTN_TRACKED_AX
PE3.Signal=GPIO_Input
PE4.GPIOParameters=GPIO_Label
PE4.GPIO_Label=BTN_MEM_SLOT
PE4.Signal=GPIO_Input
PE5.GPIOParameters=GPIO_Label
PE5.GPIO_Label=BTN_OK
PE5.Signal=GPIO_Input
PE6.GPIOParameters=GPIO_Label
PE6.GPIO_Label=BNT_SET
PE6.Signal=GPIO_Input
PE7.GPIOParameters=GPIO_Label
PE7.GPIO_Label=BTN_FREE_MOOVE
PE7.Signal=GPIO_Input
PE8.GPIOParameters=GPIO_Label
PE8.GPIO_Label=BTN_EXTERNAL_EXTRA
PE8.Signal=GPIO_Input
PE9.GPIOParameters=GPIO_Label
PE9.GPIO_Label=BTN_ONBRD_EXTRA1
PE9.Signal=GPIO_Input
PF0.GPIOParameters=GPIO_Label
PF0.GPIO_Label=MOT1_DIR
PF0.Signal=GPIO_Output
PF1.GPIOParameters=GPIO_Label
PF1.GPIO_Label=MOT1_SPREAD
PF1.Signal=GPIO_Output
PF10.GPIOParameters=GPIO_Speed,PinState,GPIO_Label
PF10.GPIO_Label=ENCODER1_CS
PF10.GPIO_Speed=GPIO_SPEED_FREQ_MEDIUM
PF10.PinState=GPIO_PIN_RESET
PF10.Signal=GPIO_Output
PF11.GPIOParameters=GPIO_Speed,GPIO_Label
PF11.GPIO_Label=ENCODER2_CS
PF11.GPIO_Speed=GPIO_SPEED_FREQ_MEDIUM
PF11.Signal=GPIO_Output
PF2.GPIOParameters=GPIO_Label
PF2.GPIO_Label=MOT1_MS1
PF2.Signal=GPIO_Output
PF3.GPIOParameters=GPIO_Label
PF3.GPIO_Label=MOT1_MS2
PF3.Signal=GPIO_Output
PF4.GPIOParameters=GPIO_Label
PF4.GPIO_Label=MOT2_DIR
PF4.Signal=GPIO_Output
PF5.GPIOParameters=GPIO_Label
PF5.GPIO_Label=MOT2_SPREAD
PF5.Signal=GPIO_Output
PF6.GPIOParameters=GPIO_Label
PF6.GPIO_Label=MOT2_MS1
PF6.Signal=GPIO_Output
PF7.GPIOParameters=GPIO_Label
PF7.GPIO_Label=MOT2_MS2
PF7.Signal=GPIO_Output
PF8.GPIOParameters=GPIO_Label
PF8.GPIO_Label=MOT_ENN
PF8.Signal=GPIO_Output
PF9.GPIOParameters=GPIO_Label
PF9.GPIO_Label=OLED_RES
PF9.Signal=GPIO_Output
PG11.GPIOParameters=GPIO_Label
PG11.GPIO_Label=RMII_TX_EN [LAN8742A-CZ-TR_TXEN]
PG11.Mode=RMII
PG11.Signal=ETH_TX_EN
PG13.GPIOParameters=GPIO_Label
PG13.GPIO_Label=RMII_TXD0 [LAN8742A-CZ-TR_TXD0]
PG13.Mode=RMII
PG13.Signal=ETH_TXD0
PG7.GPIOParameters=GPIO_Label
PG7.GPIO_Label=USB_OverCurrent [STMPS2151STR_FAULT]
PG7.Signal=GPIO_Input
PG9.Mode=Full_Duplex_Master
PG9.Signal=SPI1_MISO
PH0/OSC_IN.GPIOParameters=GPIO_Label
PH0/OSC_IN.GPIO_Label=MCO [STM32F103CBT6_PA8]
PH0/OSC_IN.Mode=HSE-External-Clock-Source
PH0/OSC_IN.Signal=RCC_OSC_IN
PH1/OSC_OUT.Mode=HSE-External-Clock-Source
PH1/OSC_OUT.Signal=RCC_OSC_OUT
RCC.HSE_VALUE=8000000
RCC.SYSCLKFreq_VALUE=96000000
RCC.SYSCLKSource=RCC_SYSCLKSOURCE_PLLCLK
RCC.SYSCLKSourceVirtual=RCC_SYSCLKSOURCE_PLLCLK
board=NUCLEO-F767ZI
boardIOC=true

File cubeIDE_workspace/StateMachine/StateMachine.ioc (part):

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Mcu.Name=STM32F446R(C-E)Tx
Mcu.Package=LQFP64
Mcu.UserName=STM32F446RETx
PA0-WKUP.GPIOParameters=GPIO_Label
PA0-WKUP.GPIO_Label=ADC_NUMPAD
PA0-WKUP.Signal=ADCx_IN0
PA13.GPIOParameters=GPIO_Label
PA13.GPIO_Label=TMS
PA13.Mode=Serial_Wire
PA13.Signal=SYS_JTMS-SWDIO
PA14.GPIOParameters=GPIO_Label
PA14.GPIO_Label=TCK
PA14.Mode=Serial_Wire
PA14.Signal=SYS_JTCK-SWCLK
PA2.GPIOParameters=GPIO_Label
PA2.GPIO_Label=USART_TX
PA2.Mode=Asynchronous
PA2.Signal=USART2_TX
PA3.GPIOParameters=GPIO_Label
PA3.GPIO_Label=USART_RX
PA3.Mode=Asynchronous
PA3.Signal=USART2_RX
PA5.GPIOParameters=GPIO_Label
PA5.GPIO_Label=LD2 [Green Led]
PA5.Signal=GPIO_Output
PA8.GPIOParameters=GPIO_PuPd,GPIO_Label
PA8.GPIO_Label=PURPLE_BTN
PA8.GPIO_PuPd=GPIO_PULLDOWN
PA8.Signal=GPIO_Input
PA9.GPIOParameters=GPIO_PuPd,GPIO_Label
PA9.GPIO_Label=PINK_BTN
PA9.GPIO_PuPd=GPIO_PULLDOWN
PA9.Signal=GPIO_Input
PB10.GPIOParameters=GPIO_PuPd,GPIO_Label
PB10.GPIO_Label=BLUE_BTN
PB10.GPIO_PuPd=GPIO_PULLDOWN
PB10.Signal=GPIO_Input
PB3.GPIOParameters=GPIO_Label
PB3.GPIO_Label=SWO
PB3.Signal=SYS_JTDO-SWO
PB4.GPIOParameters=GPIO_PuPd,GPIO_Label
PB4.GPIO_Label=GREEN_BTN
PB4.GPIO_PuPd=GPIO_PULLDOWN
PB4.Signal=GPIO_Input
PB8.Mode=I2C
PB8.Signal=I2C1_SCL
PB9.Mode=I2C
PB9.Signal=I2C1_SDA
PC13.GPIOParameters=GPIO_Label,GPIO_ModeDefaultEXTI
PC13.GPIO_Label=B1 [Blue PushButton]
PC13.GPIO_ModeDefaultEXTI=GPIO_MODE_IT_FALLING
PC13.Signal=GPXTI13
PC14-OSC32_IN.Mode=LSE-External-Oscillator
PC14-OSC32_IN.Signal=RCC_OSC32_IN
PC15-OSC32_OUT.Mode=LSE-External-Oscillator
PC15-OSC32_OUT.Signal=RCC_OSC32_OUT
PC7.GPIOParameters=GPIO_Label
PC7.GPIO_Label=OLED_RESET_NOT
PC7.Signal=GPIO_Output
PH0-OSC_IN.Mode=HSE-External-Oscillator
PH0-OSC_IN.Signal=RCC_OSC_IN
PH1-OSC_OUT.Mode=HSE-External-Oscillator
PH1-OSC_OUT.Signal=RCC_OSC_OUT
RCC.HSE_VALUE=8000000
RCC.SYSCLKFreq_VALUE=84000000
RCC.SYSCLKSource=RCC_SYSCLKSOURCE_PLLCLK
board=NUCLEO-F446RE
boardIOC=true
